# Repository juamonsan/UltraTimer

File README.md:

# UltraTimer
A custom PCB board with a STM32 microcontroller, 7 seg display, a buzzer and many leds... In the shape of the #1 hero of all galaxy. Made with [KiCAD](https://www.kicad.org/), [Inkscape](https://inkscape.org/), [Gingerbread](https://github.com/wntrblm/Gingerbread) and [Stretch](https://github.com/JarrettR/Stretch). Programmed with [STM32CubeIDE](https://www.st.com/en/development-tools/stm32cubeide.html).

WORK IN PROGRESS!!

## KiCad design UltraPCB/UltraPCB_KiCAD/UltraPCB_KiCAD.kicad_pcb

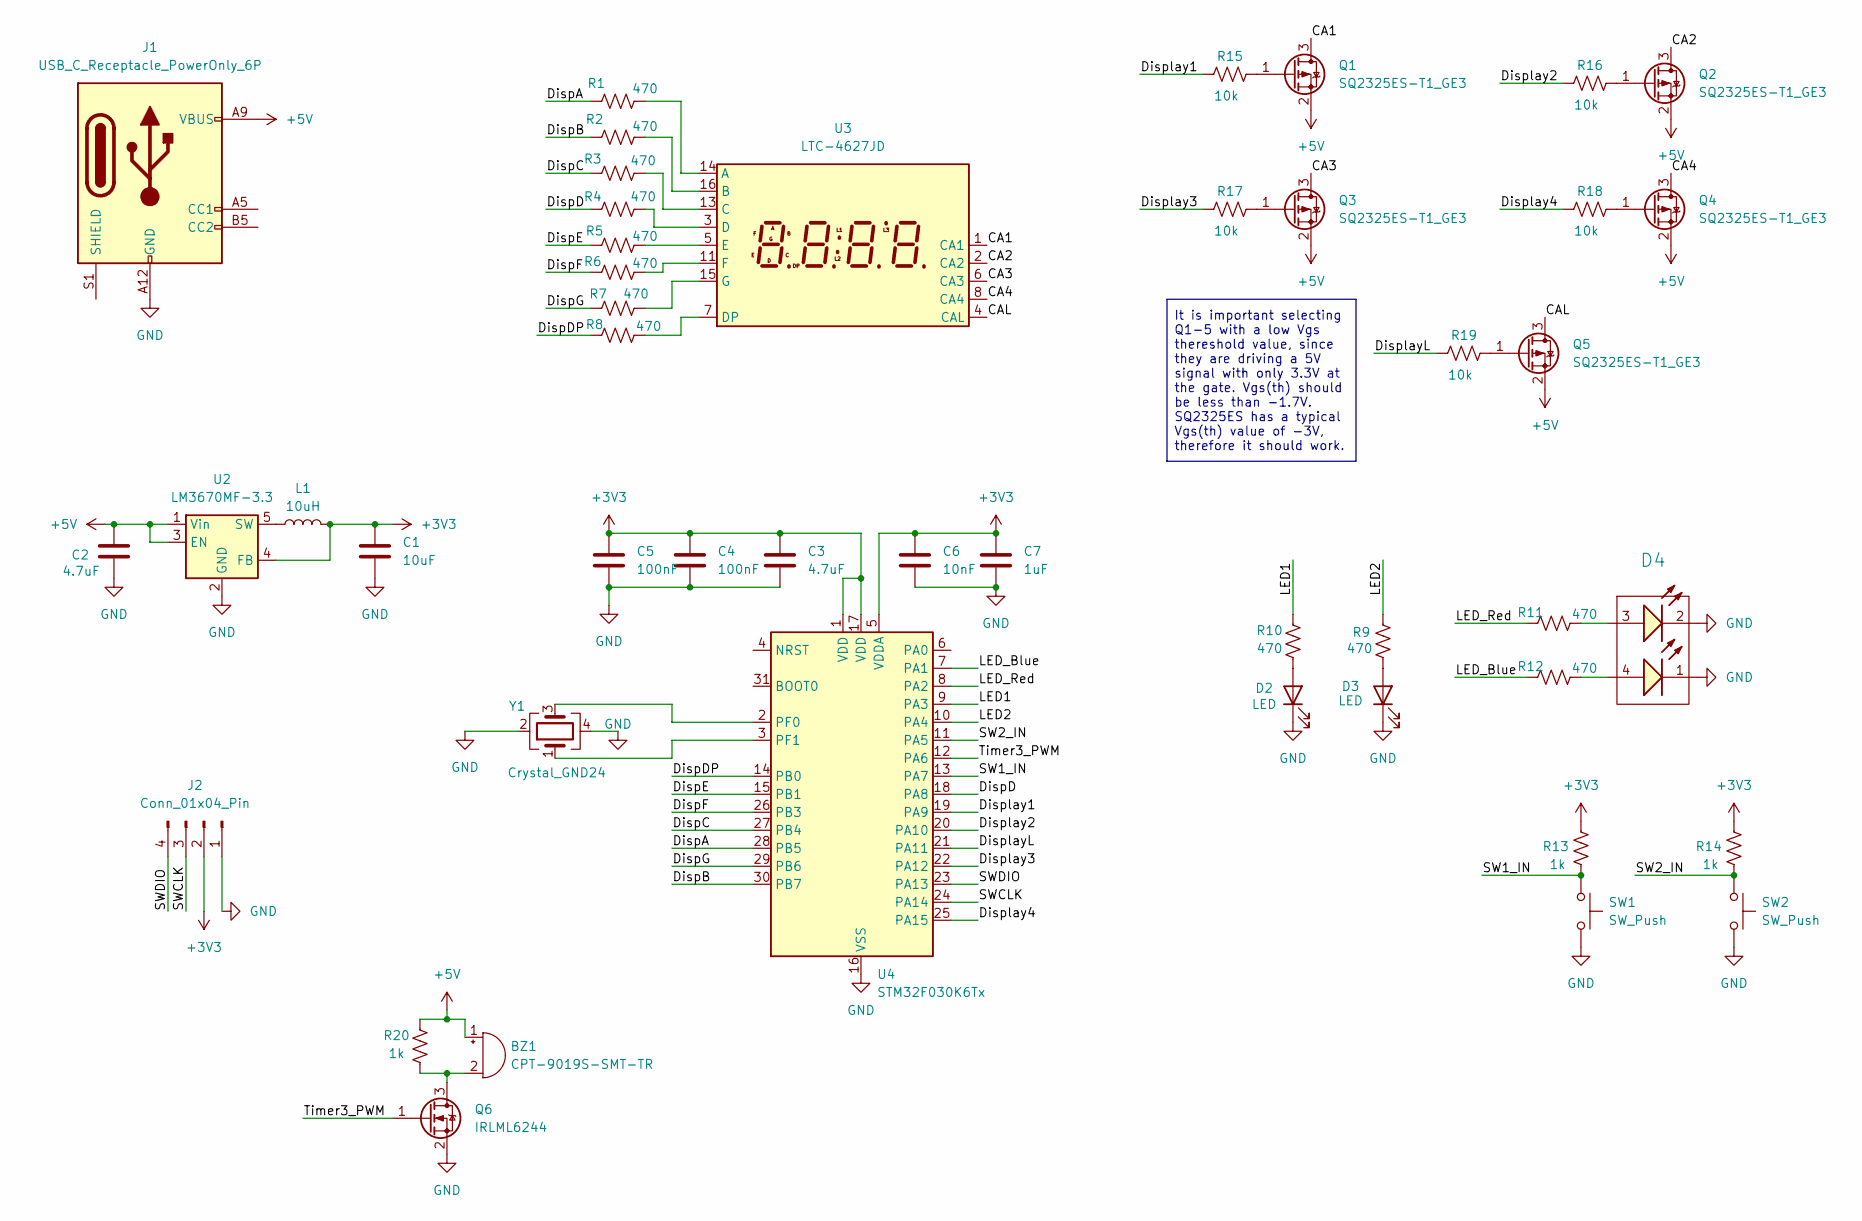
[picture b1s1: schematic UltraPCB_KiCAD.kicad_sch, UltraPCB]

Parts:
BZ1: CPT-9019S-SMT-TR; Buzzer_CUI_CPT-9019S-SMT
C1: 10uF; C_0603_1608Metric_Pad1.08x0.95mm_HandSolder
C2, C3: 4.7uF; C_0603_1608Metric_Pad1.08x0.95mm_HandSolder
C4, C5: 100nF; C_0603_1608Metric_Pad1.08x0.95mm_HandSolder
C6: 10nF; C_0603_1608Metric_Pad1.08x0.95mm_HandSolder
C7: 1uF; C_0603_1608Metric_Pad1.08x0.95mm_HandSolder
D2, D3: LED; LED_0805_2012Metric_Pad1.15x1.40mm_HandSolder
D4: Red & Blue, 120°; WL-SBRW_1205_reverse mount; Forward Voltage (Blue) 3.3V; Forward Voltage (Red) 2V; Manufacturer Part Number 156125RB73000
J1: USB_C_Receptacle_PowerOnly_6P; USB_C_Receptacle_GCT_USB4125-xx-x-0190_6P_TopMnt_Horizontal
J2: Conn_01x04_Pin; PinHeader_1x04_P2.54mm_Vertical_SMD_Pin1Right
L1: 10uH; L_0603_1608Metric_Pad1.05x0.95mm_HandSolder
Q1, Q2, Q3, Q4, Q5: SQ2325ES-T1_GE3; SOT-23
Q6: IRLML6244; SOT-23
R1, R2, R3, R4, R5, R6, R7, R8, R9, R10, R11, R12: 470; R_0603_1608Metric_Pad0.98x0.95mm_HandSolder
R13, R14, R20: 1k; R_0603_1608Metric_Pad0.98x0.95mm_HandSolder
R15, R16, R17, R18, R19: 10k; R_0603_1608Metric_Pad0.98x0.95mm_HandSolder
SW1, SW2: SW_Push; SW_SPST_Omron_B3FS-100xP
U2: LM3670MF-3.3; TSOT-23-5
U3: LTC-4627JD; LTC-4627Jx
U4: STM32F030K6Tx; LQFP-32_7x7mm_P0.8mm
Y1: Crystal_GND24; Crystal_SMD_3225-4Pin_3.2x2.5mm

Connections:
+3V3: C1.1, C3.1, C4.1, C5.1, C6.1, C7.1, J2.2, L1.2, R13.2, R14.2, U2.4 (FB), U4.1 (VDD), U4.5 (VDDA), U4.17 (VDD)
+5V: BZ1.1 (+), C2.1, J1.A9 (VBUS), J1.B9 (VBUS), Q1.2 (S), Q2.2 (S), Q3.2 (S), Q4.2 (S), Q5.2 (S), R20.2, U2.1 (Vin), U2.3 (EN)
/CA1: Q1.3 (D), U3.1 (CA1)
/CA2: Q2.3 (D), U3.2 (CA2)
/CA3: Q3.3 (D), U3.6 (CA3)
/CA4: Q4.3 (D), U3.8 (CA4)
/CAL: Q5.3 (D), U3.4 (CAL)
/DispA: R1.1, U4.28 (PB5)
/DispB: R2.1, U4.30 (PB7)
/DispC: R3.1, U4.27 (PB4)
/DispD: R4.1, U4.18 (PA8)
/DispDP: R8.1, U4.14 (PB0)
/DispE: R5.1, U4.15 (PB1)
/DispF: R6.1, U4.26 (PB3)
/DispG: R7.1, U4.29 (PB6)
/Display1: R15.2, U4.19 (PA9)
/Display2: R16.2, U4.20 (PA10)
/Display3: R17.2, U4.22 (PA12)
/Display4: R18.2, U4.25 (PA15)
/DisplayL: R19.2, U4.21 (PA11)
/LED1: R10.2, U4.9 (PA3)
/LED2: R9.2, U4.10 (PA4)
/LED_Blue: R12.1, U4.7 (PA1)
/LED_Red: R11.1, U4.8 (PA2)
/SW1_IN: R13.1, SW1.1, U4.13 (PA7)
/SW2_IN: R14.1, SW2.1, U4.11 (PA5)
/SWCLK: J2.3, U4.24 (PA14)
/SWDIO: J2.4, U4.23 (PA13)
/Timer3_PWM: Q6.1 (G), U4.12 (PA6)
GND: C1.2, C2.2, C3.2, C4.2, C5.2, C6.2, C7.2, D2.1 (K), D3.1 (K), D4.1 (K), D4.2 (K), J1.A12 (GND), J1.B12 (GND), J2.1, Q6.2 (S), SW1.2, SW2.2, U2.2 (GND), U4.16 (VSS), U4.32 (VSS), Y1.2, Y1.4
unnamed: BZ1.2 (-), Q6.3 (D), R20.1
unnamed: D2.2 (A), R10.1
unnamed: D3.2 (A), R9.1
unnamed: D4.3 (A), R11.2
unnamed: D4.4 (A), R12.2
unnamed: Q1.1 (G), R15.1
unnamed: Q2.1 (G), R16.1
unnamed: Q3.1 (G), R17.1
unnamed: Q4.1 (G), R18.1
unnamed: Q5.1 (G), R19.1
unnamed: L1.1, U2.5 (SW)
unnamed: R1.2, U3.14 (A)
unnamed: R2.2, U3.16 (B)
unnamed: R3.2, U3.13 (C)
unnamed: R4.2, U3.3 (D)
unnamed: R8.2, U3.7 (DP)
unnamed: R5.2, U3.5 (E)
unnamed: R6.2, U3.11 (F)
unnamed: R7.2, U3.15 (G)
unnamed: U4.2 (PF0), Y1.3
unnamed: U4.3 (PF1), Y1.1

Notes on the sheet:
It is important selecting Q1-5 with a low Vgs thereshold value, since they are driving a 5V signal with only 3.3V at the gate. Vgs(th) should be less than -1.7V. SQ2325ES has a typical Vgs(th) value of -3V, therefore it should work.

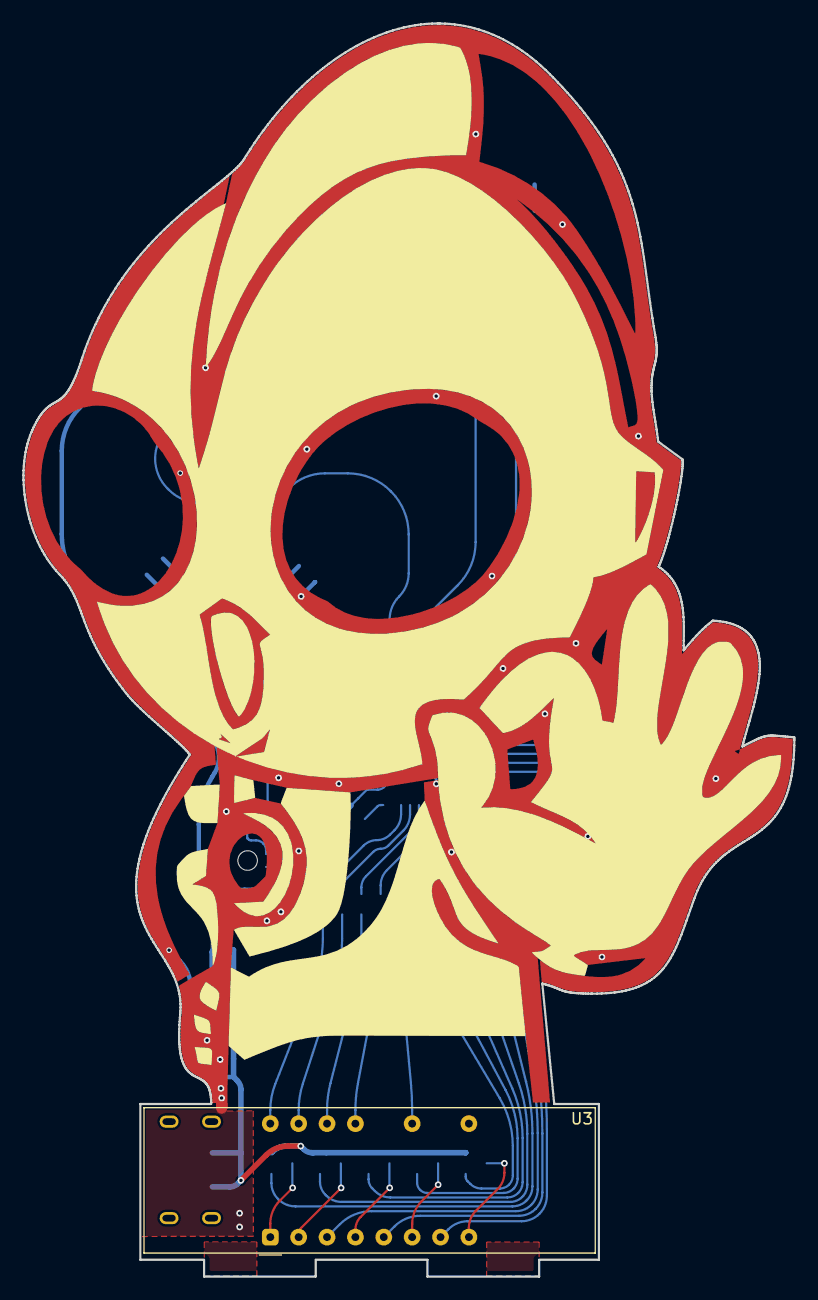
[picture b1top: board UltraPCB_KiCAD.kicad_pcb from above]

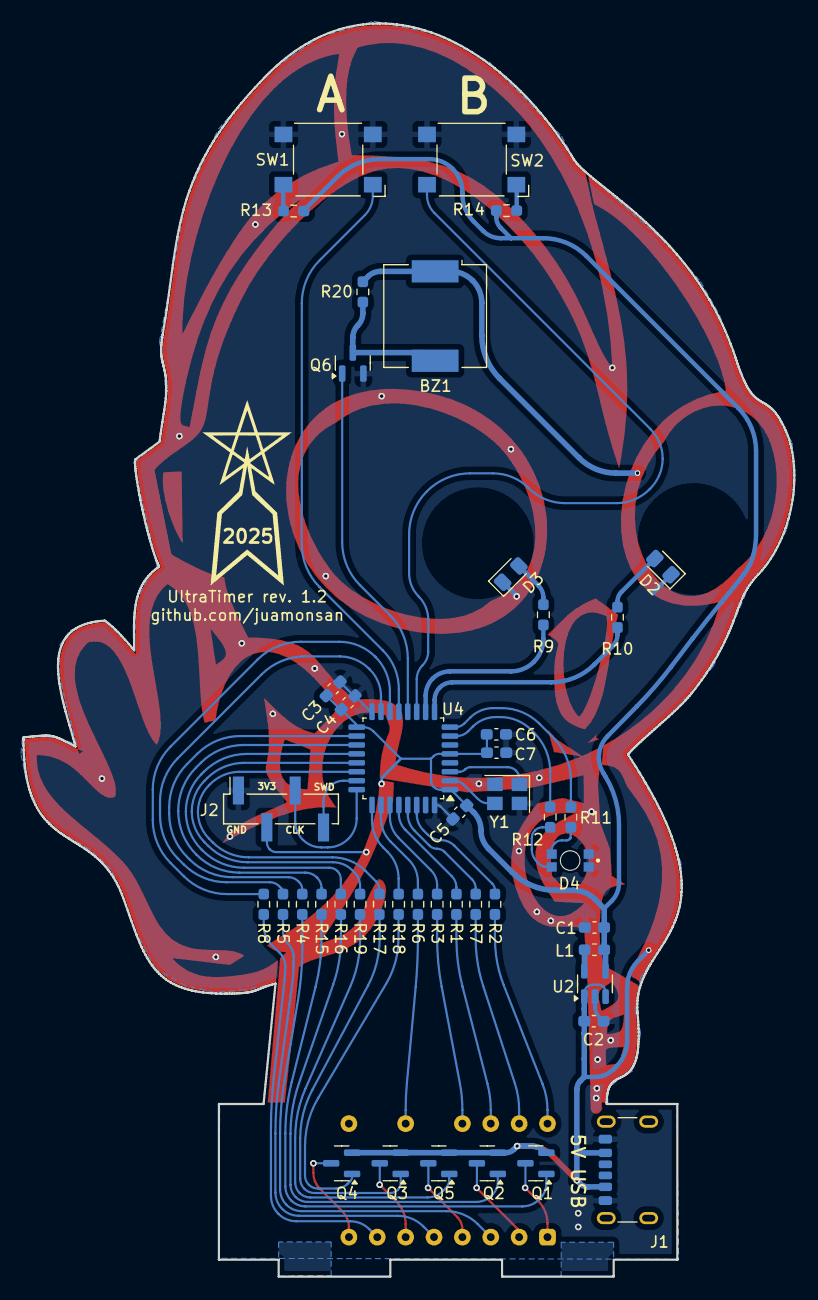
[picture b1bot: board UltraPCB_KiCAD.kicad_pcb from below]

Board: 2 copper layers, 69.0 x 112.2 mm, 46 parts (45 on the bottom side), 51 nets.

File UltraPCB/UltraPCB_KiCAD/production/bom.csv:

"Reference","Value","Datasheet","Footprint","Qty","DNP","Supplier1","SupplierPartNumber1"
"BZ1","CPT-9019S-SMT-TR","~","Buzzer_Beeper:Buzzer_CUI_CPT-9019S-SMT","1","","Mouser"," 490-CPT-9019S-SMT-TR "
"C1","10uF","~","Capacitor_SMD:C_0603_1608Metric_Pad1.08x0.95mm_HandSolder","1","","Mouser"," 81-GRM188R60J106KE7D "
"C2,C3","4.7uF","~","Capacitor_SMD:C_0603_1608Metric_Pad1.08x0.95mm_HandSolder","2","","Mouser"," 81-GRM185C80J475ME1D "
"C4,C5","100nF","~","Capacitor_SMD:C_0603_1608Metric_Pad1.08x0.95mm_HandSolder","2","","Mouser"," 81-GCJ188R71C104MA1D "
"C6","10nF","~","Capacitor_SMD:C_0603_1608Metric_Pad1.08x0.95mm_HandSolder","1","","Mouser"," 81-GCJ188R71E103KA1D "
"C7","1uF","~","Capacitor_SMD:C_0603_1608Metric_Pad1.08x0.95mm_HandSolder","1","","Mouser"," 81-GRM39R105K10 "
"D2,D3","LED","~","LED_SMD:LED_0805_2012Metric_Pad1.15x1.40mm_HandSolder","2","","Mouser"," 710-150080AS75000 "
"D4","Red & Blue, 120°","","WL-SBRW_1205_reverse mount","1","","Mouser"," 710-156125RB73000 "
"J1","USB_C_Receptacle_PowerOnly_6P","https://www.usb.org/sites/default/files/documents/usb_type-c.zip","Connector_USB:USB_C_Receptacle_GCT_USB4125-xx-x-0190_6P_TopMnt_Horizontal","1","","Mouser"," 179-UJCHGSMT2P6TR "
"J2","Conn_01x04_Pin","~","Connector_PinHeader_2.54mm:PinHeader_1x04_P2.54mm_Vertical_SMD_Pin1Right","1","","Mouser"," 855-M20-8770446 "
"L1","10uH","~","Inductor_SMD:L_0603_1608Metric_Pad1.05x0.95mm_HandSolder","1","","Mouser"," 963-CBMF1608T100K "
"Q1,Q2,Q3,Q4,Q5","IRLML6401","https://www.infineon.com/dgdl/irlml6401pbf.pdf?fileId=5546d4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","Package_TO_SOT_SMD:SOT-23","5","","Mouser"," 942-IRLML6401TRPBF "
"Q6","IRLML6244","https://www.infineon.com/dgdl/Infineon-IRLML6244-DataSheet-v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","Package_TO_SOT_SMD:SOT-23","1","","Mouser","942-IRLML6244TRPBF "
"R1,R2,R3,R4,R5,R6,R7,R8,R9,R10,R11,R12","470","~","Resistor_SMD:R_0603_1608Metric_Pad0.98x0.95mm_HandSolder","12","","Mouser"," 603-AC0603FR-7W470RL "
"R13,R14,R20","1k","~","Resistor_SMD:R_0603_1608Metric_Pad0.98x0.95mm_HandSolder","3","","Mouser"," 603-AC0603FR-7W1KL "
"R15,R16,R17,R18,R19","10k","~","Resistor_SMD:R_0603_1608Metric_Pad0.98x0.95mm_HandSolder","5","","Mouser"," 603-RC0603FR-7W10KL "
"SW1,SW2","SW_Push","~","Button_Switch_SMD:SW_SPST_Omron_B3FS-100xP","2","","Mouser","653-B3FS-1000"
"U2","LM3670MF-3.3","http://www.ti.com/lit/ds/symlink/lm3670.pdf","Package_TO_SOT_SMD:TSOT-23-5","1","","Mouser"," 926-LM3670MF33NOPB "
"U3","LTC-4627JD","http://optoelectronics.liteon.com/upload/download/DS30-2001-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","Display_7Segment:LTC-4627Jx","1","","Mouser"," 859-LTC-4627JD "
"U4","STM32F030K6Tx","https://www.st.com/resource/en/datasheet/stm32f030k6.pdf","Package_QFP:LQFP-32_7x7mm_P0.8mm","1","","Mouser"," 511-STM32F030K6T6TR "

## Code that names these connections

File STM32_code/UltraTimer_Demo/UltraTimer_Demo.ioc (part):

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Mcu.Name=STM32F030K6Tx
Mcu.Package=LQFP32
Mcu.UserName=STM32F030K6Tx
PA10.GPIOParameters=PinState,GPIO_PuPd,GPIO_Label
PA10.GPIO_Label=Display2
PA10.GPIO_PuPd=GPIO_NOPULL
PA10.PinState=GPIO_PIN_RESET
PA10.Signal=GPIO_Output
PA11.GPIOParameters=PinState,GPIO_PuPd,GPIO_Label
PA11.GPIO_Label=DisplayL
PA11.GPIO_PuPd=GPIO_NOPULL
PA11.PinState=GPIO_PIN_RESET
PA11.Signal=GPIO_Output
PA12.GPIOParameters=PinState,GPIO_PuPd,GPIO_Label
PA12.GPIO_Label=Display3
PA12.GPIO_PuPd=GPIO_NOPULL
PA12.PinState=GPIO_PIN_RESET
PA12.Signal=GPIO_Output
PA13.Mode=Serial_Wire
PA13.Signal=SYS_SWDIO
PA14.Mode=Serial_Wire
PA14.Signal=SYS_SWCLK
PA15.GPIOParameters=PinState,GPIO_PuPd,GPIO_Label,GPIO_ModeDefaultOutputPP
PA15.GPIO_Label=Display4
PA15.GPIO_ModeDefaultOutputPP=GPIO_MODE_OUTPUT_PP
PA15.GPIO_PuPd=GPIO_NOPULL
PA15.PinState=GPIO_PIN_RESET
PA15.Signal=GPIO_Output
PA3.GPIOParameters=GPIO_Label
PA3.GPIO_Label=LED1
PA3.Signal=GPIO_Output
PA4.GPIOParameters=GPIO_Label
PA4.GPIO_Label=LED2
PA4.Signal=GPIO_Output
PA5.GPIOParameters=GPIO_PuPd,GPIO_Label,GPIO_ModeDefaultEXTI
PA5.GPIO_Label=B_Button_EXTI
PA5.GPIO_ModeDefaultEXTI=GPIO_MODE_IT_FALLING
PA5.GPIO_PuPd=GPIO_PULLDOWN
PA5.Signal=GPXTI5
PA6.GPIOParameters=GPIO_Label
PA6.GPIO_Label=Timer3_PWM
PA6.Signal=S_TIM3_CH1
PA7.GPIOParameters=GPIO_PuPd,GPIO_Label,GPIO_ModeDefaultEXTI
PA7.GPIO_Label=A_Button_EXTI
PA7.GPIO_ModeDefaultEXTI=GPIO_MODE_IT_FALLING
PA7.GPIO_PuPd=GPIO_PULLDOWN
PA7.Signal=GPXTI7
PA8.GPIOParameters=PinState,GPIO_PuPd,GPIO_Label
PA8.GPIO_Label=DispD
PA8.GPIO_PuPd=GPIO_NOPULL
PA8.PinState=GPIO_PIN_RESET
PA8.Signal=GPIO_Output
PA9.GPIOParameters=PinState,GPIO_PuPd,GPIO_Label,GPIO_ModeDefaultOutputPP
PA9.GPIO_Label=Display1
PA9.GPIO_ModeDefaultOutputPP=GPIO_MODE_OUTPUT_PP
PA9.GPIO_PuPd=GPIO_NOPULL
PA9.PinState=GPIO_PIN_RESET
PA9.Signal=GPIO_Output
PB0.GPIOParameters=GPIO_Label
PB0.GPIO_Label=DispDP
PB0.Signal=GPIO_Output
PB1.GPIOParameters=GPIO_Label
PB1.GPIO_Label=DispE
PB1.Signal=GPIO_Output
PB3.GPIOParameters=GPIO_Label
PB3.GPIO_Label=DispF
PB3.Signal=GPIO_Output
PB4.GPIOParameters=GPIO_Label
PB4.GPIO_Label=DispC
PB4.Signal=GPIO_Output
PB5.GPIOParameters=GPIO_Label
PB5.GPIO_Label=DispA
PB5.Signal=GPIO_Output
PB6.GPIOParameters=GPIO_Label
PB6.GPIO_Label=DispG
PB6.Signal=GPIO_Output
PB7.GPIOParameters=GPIO_Label
PB7.GPIO_Label=DispB
PB7.Signal=GPIO_Output
PF0-OSC_IN.GPIOParameters=GPIO_Label
PF0-OSC_IN.GPIO_Label=LED_Blue
PF0-OSC_IN.Signal=GPIO_Output
PF1-OSC_OUT.GPIOParameters=GPIO_Label
PF1-OSC_OUT.GPIO_Label=LED_Red
PF1-OSC_OUT.Signal=GPIO_Output
board=custom

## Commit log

2024-10-13 Added KiCAD project 1.0
2024-10-21 New components
    D1, SW1-2 changed. Mounting pads added. Minor improvements.
2024-10-23 Production ready v1.0
    Added production files. Components now have mouser part numbers. 7seg display was upside down so it was corrected. All production ready.
2024-10-23 Documentation added
    PDF and interactive html bom added
2024-10-25 Rev. 1.1
    Error correction and new folder structure for production files
2025-02-11 STEP file added
2025-02-12 3D files for easy stencil
2025-02-13 Revision 1.2
2025-02-13 STM32 demo project created
2025-02-15 Buzzer and 7seg testing
2025-02-15 Button handler
2025-02-15 More button testing
2025-02-25 main.c corrections
2025-03-02 Q1-5 replaced
2025-03-25 Use function DisplayNumber()
2025-04-16 Changed to KiCAD 9 and rounded all tracks
    Plugin Round Tracks was used for automatically rounding all tracks
2025-04-20 Added quartz
